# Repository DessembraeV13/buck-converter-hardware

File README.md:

# Przetwornica DC/DC Buck 60V na 5V / 30A z Cyfrowym Sterowaniem
### _High-Power 60V to 5V / 30A Buck Converter with Digital Control Interface_

Projekt i realizacja wysokoprądowej, wysokonapięciowej przetwornicy impulsowej typu Synchronous Buck, zrealizowanej w oprogramowaniu **KiCAD**. Projekt obejmował pełen cykl tworzenia hardware'u: od definicji założeń, przez dobór komponentów, projekt schematu ideowego, aż po projekt wielowarstwowej płytki PCB i uruchomienie fizycznego prototypu.

Celem było stworzenie platformy sprzętowej zdolnej do wydajnej konwersji mocy, przygotowanej do współpracy z mikrokontrolerem w celu cyfrowego sterowania parametrami wyjściowymi.

<div align="center">
  
  <br>
  <em>Rys. 1. Zmontowany i uruchomiony prototyp przetwornicy.</em>
</div>

---

## Główne Założenia i Specyfikacja Techniczna

- **Topologia:** Synchroniczna przetwornica obniżająca napięcie (Synchronous Buck).
- **Napięcie wejściowe (Vin):** do **60V**.
- **Napięcie wyjściowe (Vout):** **5V** (z możliwością regulacji przez mikrokontroler).
- **Maksymalny prąd wyjściowy (Iout_max):** Projektowany do **30A**.
- **Kluczowe komponenty stopnia mocy:**
    - **Sterownik bramek MOSFET:** Texas Instruments LM5106
    - **Tranzystory MOSFET:** Texas Instruments CSD19531KCS (N-Channel NexFET)
- **Sterowanie:** Układ przygotowany do sterowania sygnałem **PWM** z mikrokontrolera (ESP32-S2).
- **Architektura zasilania logiki:** **Dwustopniowa** – pomocnicza przetwornica buck 12V (LM5164) zasila stabilizatory liniowe 5V i 3.3V, zapewniając wysoką sprawność.
- 🔩 **Interfejs komunikacyjny CAN Bus:** Płytka wyposażona w transceiver CAN (TJA1051T), przygotowany do komunikacji w standardach przemysłowych.
- **Płytka PCB:** 4-warstwowa, z dedykowanymi płaszczyznami masy i zasilania w celu optymalizacji termicznej i minimalizacji pętli prądowych.

---

## Architektura Sprzętowa

Projekt hardware'owy został podzielony na trzy oddzielne bloki funkcjonalne.

#### 1. Stopień Wysokiej Mocy
Sekcja odpowiedzialna za główną konwersję energii. Zawiera kluczowe elementy takie jak tranzystory MOSFET, sterownik bramek, cewkę wyjściową oraz kondensatory filtrujące. Projekt ścieżek na PCB w tym obszarze został zoptymalizowany pod kątem przenoszenia dużych prądów (do 30A) i minimalizacji pętli prądowych o wysokiej częstotliwości.

<div align="center">
  
  <br>
  <em>Rys. 2. Schemat ideowy stopnia mocy przetwornicy.</em>
</div>

#### 2. Układ Zasilania
Ten blok odpowiada za dostarczenie stabilnych napięć dla całej logiki cyfrowej. Został zrealizowany w wydajnej, **dwustopniowej architekturze**:
1.  **Pre-regulator:** Główne napięcie wejściowe (do 60V) jest najpierw obniżane do 12V przez dedykowaną przetwornicę buck (LM5164).
2.  **Stabilizatory LDO:** Stabilne, pośrednie napięcie 12V zasila następnie stabilizatory liniowe, które generują czyste linie 5V i 3.3V.

Taka architektura znacząco poprawia sprawność i zarządzanie ciepłem w porównaniu do próby zasilania LDO bezpośrednio z wysokiego napięcia wejściowego.

<div align="center">
  
  <br>
  <em>Rys. 3. Schemat ideowy sekcji zasilania.</em>
</div>

#### 3. Mikrokontroler i Peryferia
Logika urządzenia, oparta o mikrokontroler **ESP32-S2**. Ten blok zawiera również wszystkie interfejsy użytkownika i komunikacyjne, w tym:
- Złącza do programowania i debugowania.
- Diody LED i przyciski do interakcji z użytkownikiem.
- Transceiver magistrali CAN (TJA1051T), implementujący warstwę fizyczną dla niezawodnej komunikacji w standardach przemysłowych.

<div align="center">
  
  <br>
  <em>Rys. 4. Schemat ideowy sekcji sterowania z mikrokontrolerem i peryferiami.</em>
</div>

---

## Projekt Płytki PCB

Projekt 4-warstwowej płytki PCB był kluczowym elementem projektu, mającym na celu zapewnienie stabilności termicznej i elektrycznej przy dużych obciążeniach.

<div align="center">
  
  <br>
  <em>Rys. 5. Render 3D finalnego projektu PCB.</em>
</div>

- **Warstwa 1 (Top):** Główne ścieżki prądowe, komponenty mocy, interfejs użytkownika.
- **Warstwa 2 (GND Plane):** Lita płaszczyzna masy zapewniająca niską impedancję ścieżki powrotnej prądu i doskonałe ekranowanie.
- **Warstwa 3 (GND Plane):** Druga płaszczyzna masy dla dalszej poprawy integralności sygnałowej i odprowadzania ciepła.
- **Warstwa 4 (Bottom):** Mikrokontroler, dodatkowe komponenty, ścieżki sygnałowe.

---

## Uruchomienie i Pomiary

Prototyp został zmontowany i poddany testom w celu weryfikacji poprawności działania. Pomiary oscyloskopowe potwierdziły prawidłowe sterowanie bramek tranzystorów MOSFET. Układ został również pomyślnie przetestowany pod lekkim obciążeniem, stabilnie dostarczając napięcie wyjściowe bliskie 5V przy zasilaniu 60V.

---

## Pliki Projektowe

Pełny projekt hardware'owy (schemat, PCB) jest dostępny w folderze [`project_files/`](project_files/). Można go otworzyć za pomocą darmowego oprogramowania **KiCAD**.

_Uwaga: Oprogramowanie (firmware) dla mikrokontrolera zostało opracowane przez innego członka zespołu i nie jest częścią tego repozytorium. Zaimplementowany hardware magistrali CAN nie był wykorzystywany w finalnej wersji oprogramowania._

---

## Licencja

Ten projekt jest udostępniony na licencji MIT - zobacz plik [LICENSE](LICENSE) po szczegóły.

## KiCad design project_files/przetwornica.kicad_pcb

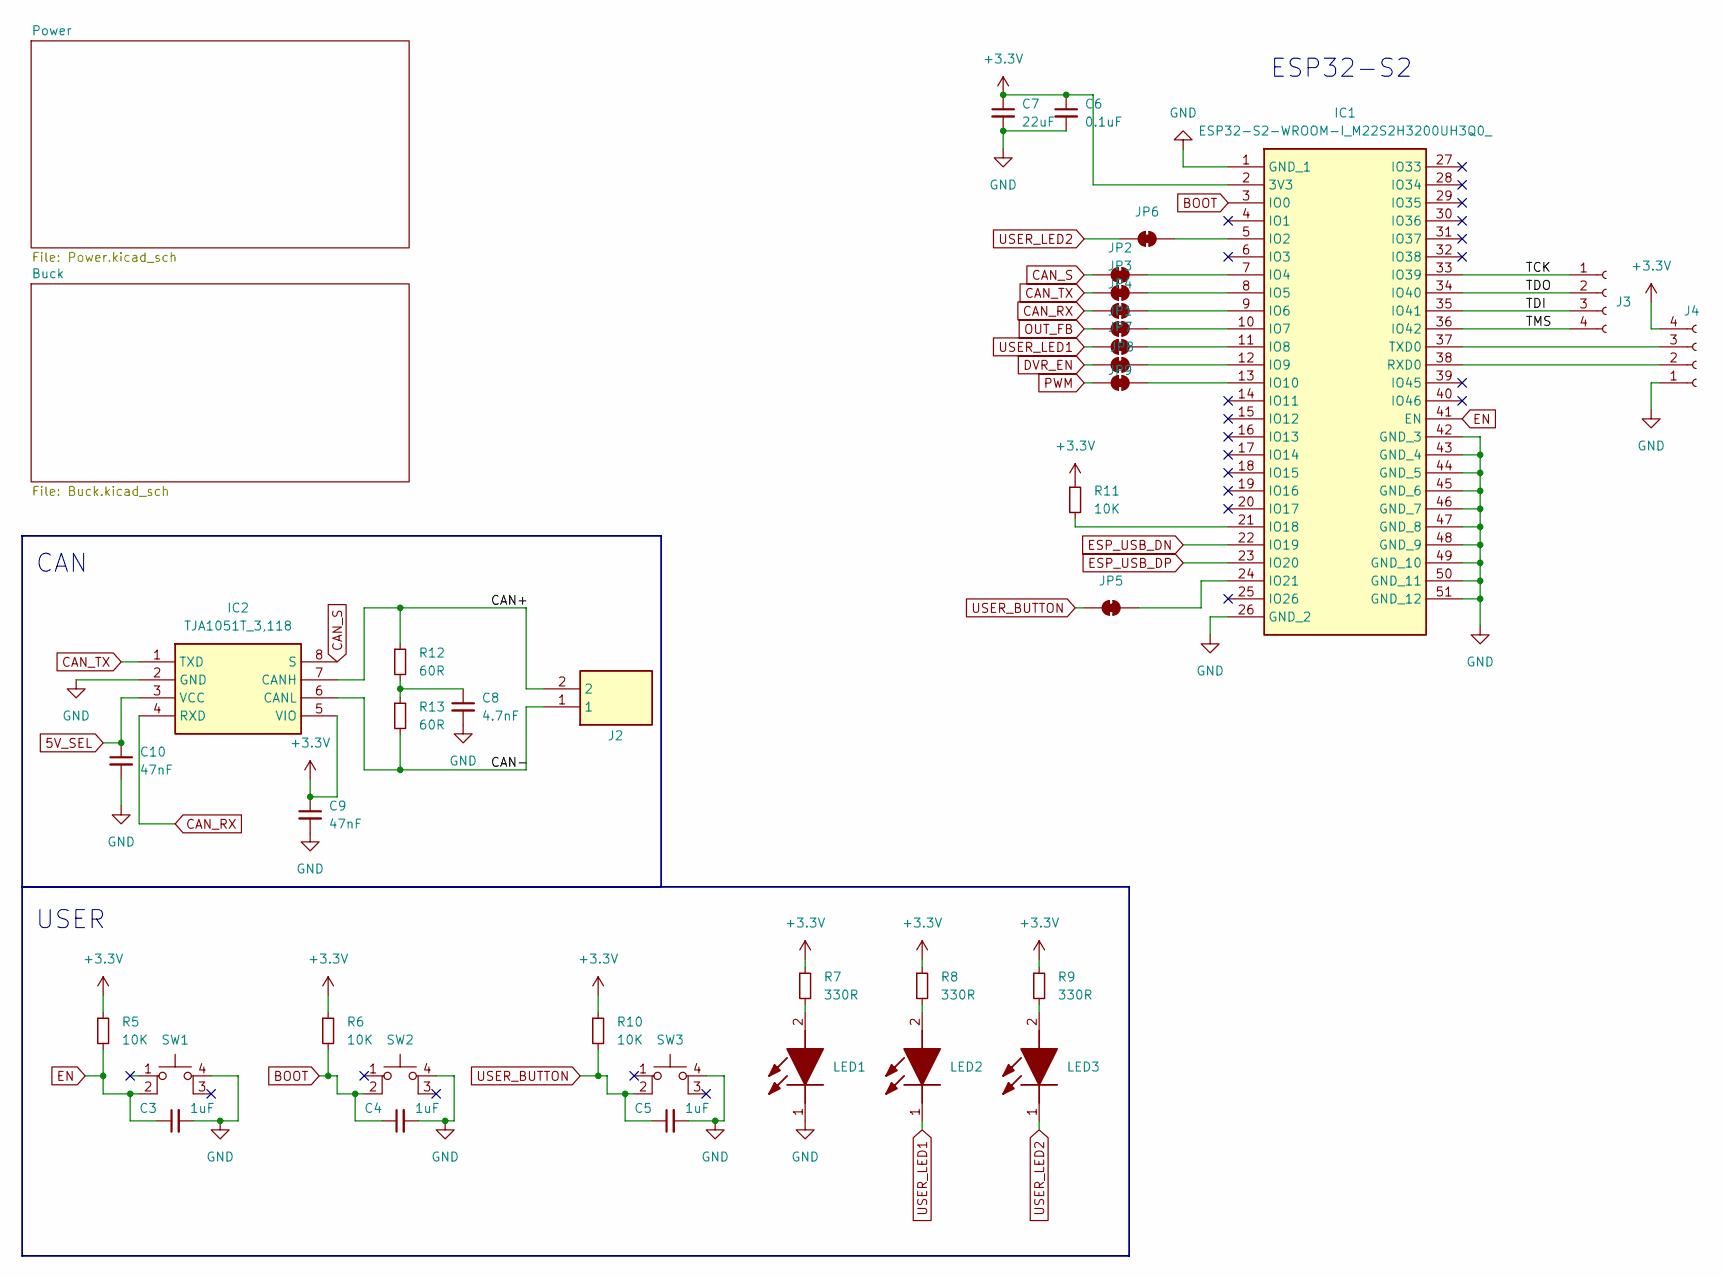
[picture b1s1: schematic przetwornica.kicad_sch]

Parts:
C3, C4, C5: 1uF; C_0805_2012Metric_Pad1.18x1.45mm_HandSolder
C6: 0.1uF; C_0805_2012Metric_Pad1.18x1.45mm_HandSolder
C7: 22uF; C_0805_2012Metric_Pad1.18x1.45mm_HandSolder
C8: 4.7nF; C_0805_2012Metric_Pad1.18x1.45mm_HandSolder
C9, C10: 47nF; C_0805_2012Metric_Pad1.18x1.45mm_HandSolder
IC1: ESP32-S2-WROOM-I_M22S2H3200UH3Q0_; ESP32S2WROOMIM22S2H3200UH3Q0; Manufacturer_Part_Number ESP32-S2-WROOM-I(M22S2H3200UH3Q0)
IC2: TJA1051T_3,118; SOIC127P600X175-8N; Manufacturer_Part_Number TJA1051T/3,118
J2: XY301V-2P__5.00_; XY301V2P500; Manufacturer_Part_Number XY301V-2P (5.00)
J3, J4: Conn_01x04_Socket; PinHeader_1x04_P2.54mm_Vertical
JP1, JP2, JP3, JP4, JP5, JP6, JP7, JP8, JP9: SolderJumper_2_Bridged; SolderJumper-2_P1.3mm_Bridged_RoundedPad1.0x1.5mm
LED1: LTST-C171KRKT; LEDM2012X90N; Manufacturer_Part_Number LTST-C171KRKT
LED2, LED3: LTST-C170KFKT; LEDC2012X120N; Manufacturer_Part_Number LTST-C170KFKT
R5, R6, R10, R11: 10K; R_0805_2012Metric_Pad1.20x1.40mm_HandSolder
R7, R8, R9: 330R; R_0805_2012Metric_Pad1.20x1.40mm_HandSolder
R12, R13: 60R; R_0805_2012Metric_Pad1.20x1.40mm_HandSolder
SW1, SW2, SW3: SW_MEC_5E; 13019319

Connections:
5V_SEL: C10.1, IC2.3 (VCC); also elsewhere on the board
+3.3V: C6.1, C7.1, C9.1, IC1.2 (3V3), IC2.5 (VIO), J4.4, R5.1, R6.1, R7.1, R8.1, R9.1, R10.1, R11.1; also elsewhere on the board
/CAN+: IC2.7 (CANH), J2.2, R12.1
/CAN-: IC2.6 (CANL), J2.1, R13.2
/TCK: IC1.33 (IO39), J3.1
/TDI: IC1.35 (IO41), J3.3
/TDO: IC1.34 (IO40), J3.2
/TMS: IC1.36 (IO42), J3.4
BOOT: C4.1, IC1.3 (IO0), R6.2, SW2.2
CAN_RX: IC2.4 (RXD), JP4.1 (A)
CAN_S: IC2.8 (S), JP2.1 (A)
CAN_TX: IC2.1 (TXD), JP3.1 (A)
DVR_EN: JP8.1 (A); also elsewhere on the board
EN: C3.1, IC1.41 (EN), R5.2, SW1.2
ESP_USB_DN: IC1.22 (IO19); also elsewhere on the board
ESP_USB_DP: IC1.23 (IO20); also elsewhere on the board
GND: C3.2, C4.2, C5.2, C6.2, C7.2, C8.2, C9.2, C10.2, IC1.1 (GND_1), IC1.26 (GND_2), IC1.42 (GND_3), IC1.43 (GND_4), IC1.44 (GND_5), IC1.45 (GND_6), IC1.46 (GND_7), IC1.47 (GND_8), IC1.48 (GND_9), IC1.49 (GND_10), IC1.50 (GND_11), IC1.51 (GND_12), IC2.2 (GND), J4.1, LED1.1 (K), SW1.4 (A), SW2.4 (A), SW3.4 (A); also elsewhere on the board
unnamed: C8.1, R12.2, R13.1
unnamed: IC1.5 (IO2), JP6.2 (B)
unnamed: IC1.7 (IO4), JP2.2 (B)
unnamed: IC1.8 (IO5), JP3.2 (B)
unnamed: IC1.9 (IO6), JP4.2 (B)
unnamed: IC1.10 (IO7), JP1.2 (B)
unnamed: IC1.11 (IO8), JP7.2 (B)
unnamed: IC1.12 (IO9), JP8.2 (B)
unnamed: IC1.13 (IO10), JP9.2 (B)
unnamed: IC1.21 (IO18), R11.2
unnamed: IC1.24 (IO21), JP5.2 (B)
unnamed: IC1.38 (RXD0), J4.2
unnamed: IC1.37 (TXD0), J4.3
unnamed: LED1.2 (A), R7.2
unnamed: LED2.2 (A), R8.2
unnamed: LED3.2 (A), R9.2
OUT_FB: JP1.1 (A); also elsewhere on the board
PWM: JP9.1 (A); also elsewhere on the board
USER_BUTTON: C5.1, JP5.1 (A), R10.2, SW3.2
USER_LED1: JP7.1 (A), LED2.1 (K)
USER_LED2: JP6.1 (A), LED3.1 (K)

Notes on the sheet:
ESP32-S2
CAN
USER

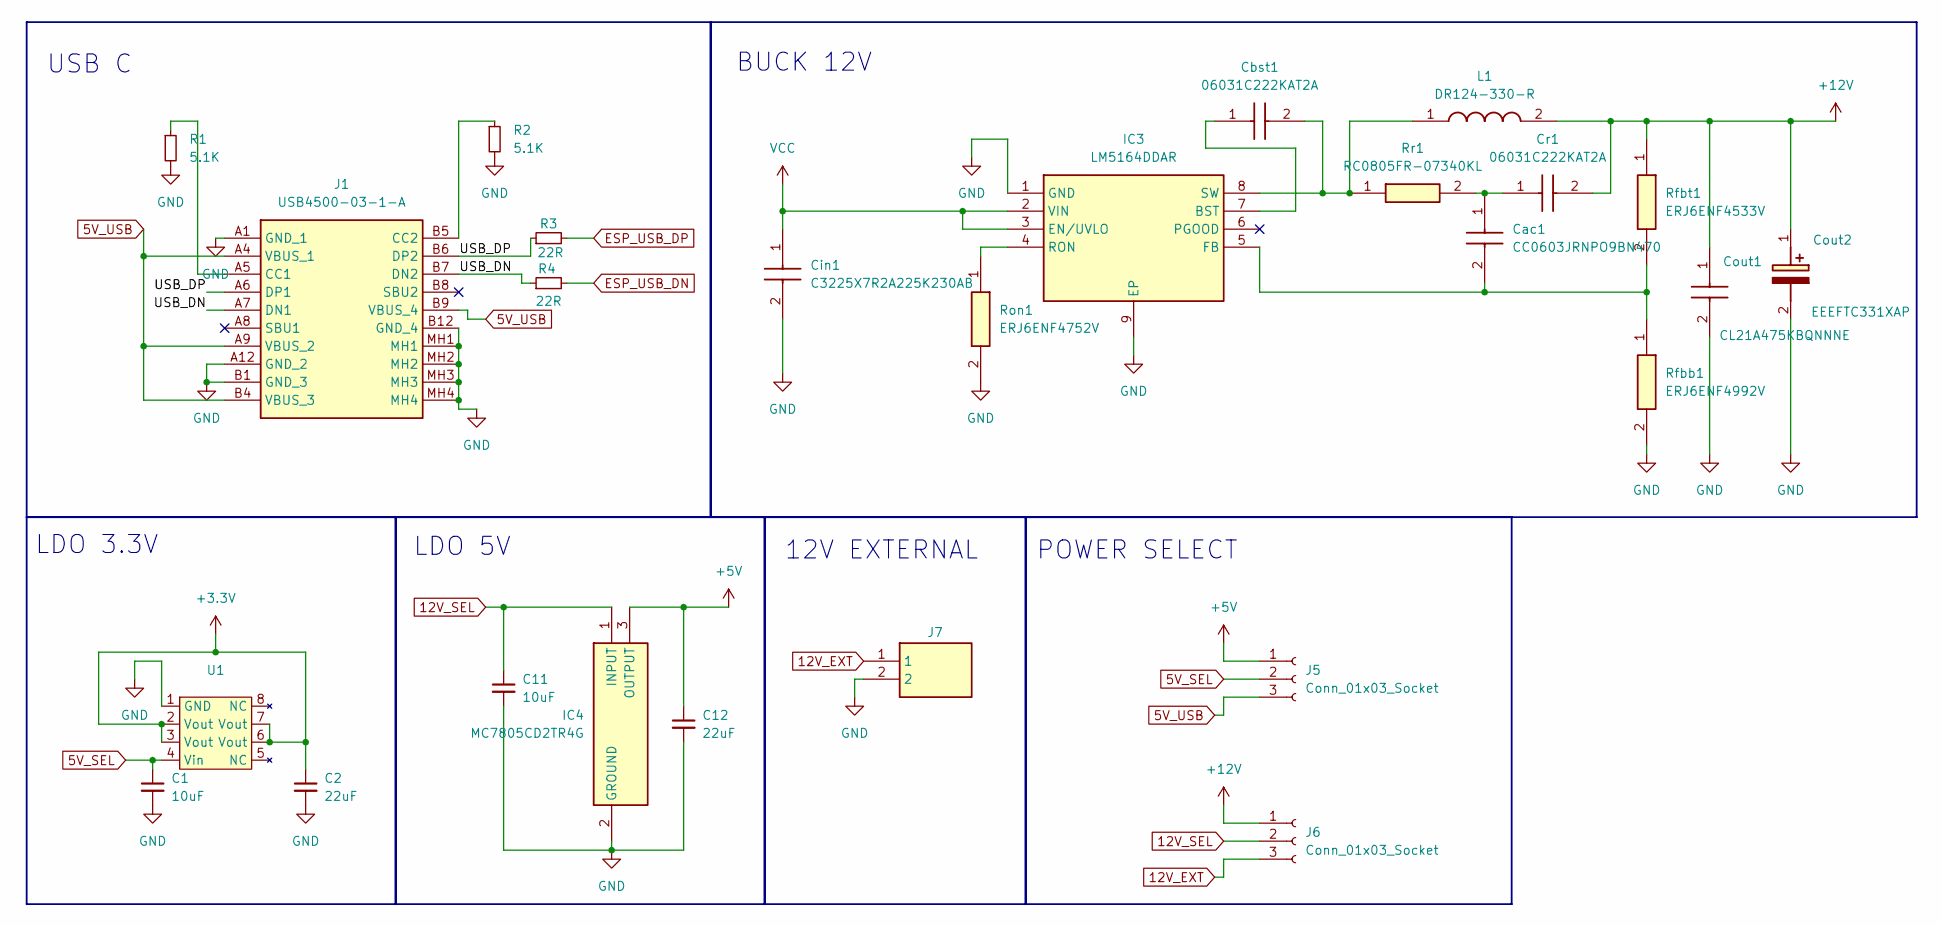
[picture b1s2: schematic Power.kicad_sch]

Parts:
C1, C11: 10uF; C_0805_2012Metric_Pad1.18x1.45mm_HandSolder
C2, C12: 22uF; C_0805_2012Metric_Pad1.18x1.45mm_HandSolder
Cac1: CC0603JRNPO9BN470; CAPC1608X90N; Manufacturer_Part_Number CC0603JRNPO9BN470
Cbst1: 06031C222KAT2A; CAPC1608X90N; Manufacturer_Part_Number 06031C222KAT2A
Cin1: C3225X7R2A225K230AB; CAPC3225X250N; Manufacturer_Part_Number C3225X7R2A225K230AB
Cout1: CL21A475KBQNNNE; CAPC2012X140N; Manufacturer_Part_Number CL21A475KBQNNNE
Cout2: EEEFTC331XAP; EEE0JA331XP; Manufacturer_Part_Number EEEFTC331XAP
Cr1: 06031C222KAT2A; CAPC1608X90N; Manufacturer_Part_Number 06031C222KAT2A
IC3: LM5164DDAR; SOIC127P600X170-9N; Manufacturer_Part_Number LM5164DDAR
IC4: MC7805CD2TR4G; Manufacturer_Part_Number MC7805CD2TR4G
J1: USB4500-03-1-A; USB4500031A; Manufacturer_Part_Number USB4500-03-1-A
J5, J6: Conn_01x03_Socket; PinHeader_1x03_P2.54mm_Vertical
J7: XY301V-2P__5.00_; XY301V2P500; Manufacturer_Part_Number XY301V-2P (5.00)
L1: DR124-330-R; DR124330R; Manufacturer_Part_Number DR124-330-R
R1, R2: 5.1K; R_0805_2012Metric_Pad1.20x1.40mm_HandSolder
R3, R4: 22R; R_0805_2012Metric_Pad1.20x1.40mm_HandSolder
Rfbb1: ERJ6ENF4992V; ERJ6ENF1000V; Manufacturer_Part_Number ERJ6ENF4992V
Rfbt1: ERJ6ENF4533V; ERJ6ENF1000V; Manufacturer_Part_Number ERJ6ENF4533V
Ron1: ERJ6ENF4752V; ERJ6ENF1000V; Manufacturer_Part_Number ERJ6ENF4752V
Rr1: RC0805FR-07340KL; ERJ6ENF1000V; Manufacturer_Part_Number ERJ6ENF4533V
U1: SO-8_3.9x4.9mm_P1.27mm

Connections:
5V_SEL: C1.1, J5.2, U1.4 (Vin); also elsewhere on the board
5V_USB: J1.A4 (VBUS_1), J1.A9 (VBUS_2), J1.B4 (VBUS_3), J1.B9 (VBUS_4), J5.3
12V_EXT: J6.3, J7.1
12V_SEL: C11.1, IC4.1 (INPUT), J6.2; also elsewhere on the board
+3.3V: C2.1, U1.2 (Vout), U1.3 (Vout), U1.6 (Vout), U1.7 (Vout); also elsewhere on the board
+5V: C12.1, IC4.3 (OUTPUT), J5.1
+12V: Cout1.1, Cout2.1 (+), Cr1.2, J6.1, L1.2, Rfbt1.1
/Power/USB_DN: J1.A7 (DN1), J1.B7 (DN2), R4.1
/Power/USB_DP: J1.A6 (DP1), J1.B6 (DP2), R3.1
ESP_USB_DN: R4.2; also elsewhere on the board
ESP_USB_DP: R3.2; also elsewhere on the board
GND: C1.2, C2.2, C11.2, C12.2, Cin1.2, Cout1.2, Cout2.2 (-), IC3.1 (GND), IC3.9 (EP), IC4.2 (GROUND), J1.A1 (GND_1), J1.A12 (GND_2), J1.B1 (GND_3), J1.B12 (GND_4), J1.MH1, J1.MH2, J1.MH3, J1.MH4, J7.2, R1.2, R2.2, Rfbb1.2, Ron1.2, U1.1 (GND); also elsewhere on the board
unnamed: Cac1.1, Cr1.1, Rr1.2
unnamed: Cbst1.1, IC3.7 (BST)
unnamed: Cac1.2, IC3.5 (FB), Rfbb1.1, Rfbt1.2
unnamed: IC3.4 (RON), Ron1.1
unnamed: Cbst1.2, IC3.8 (SW), L1.1, Rr1.1
unnamed: J1.A5 (CC1), R1.1
unnamed: J1.B5 (CC2), R2.1
VCC: Cin1.1, IC3.2 (VIN), IC3.3 (EN/UVLO); also elsewhere on the board

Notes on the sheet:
BUCK 12V
USB C
POWER SELECT
LDO 5V
12V EXTERNAL
LDO 3.3V

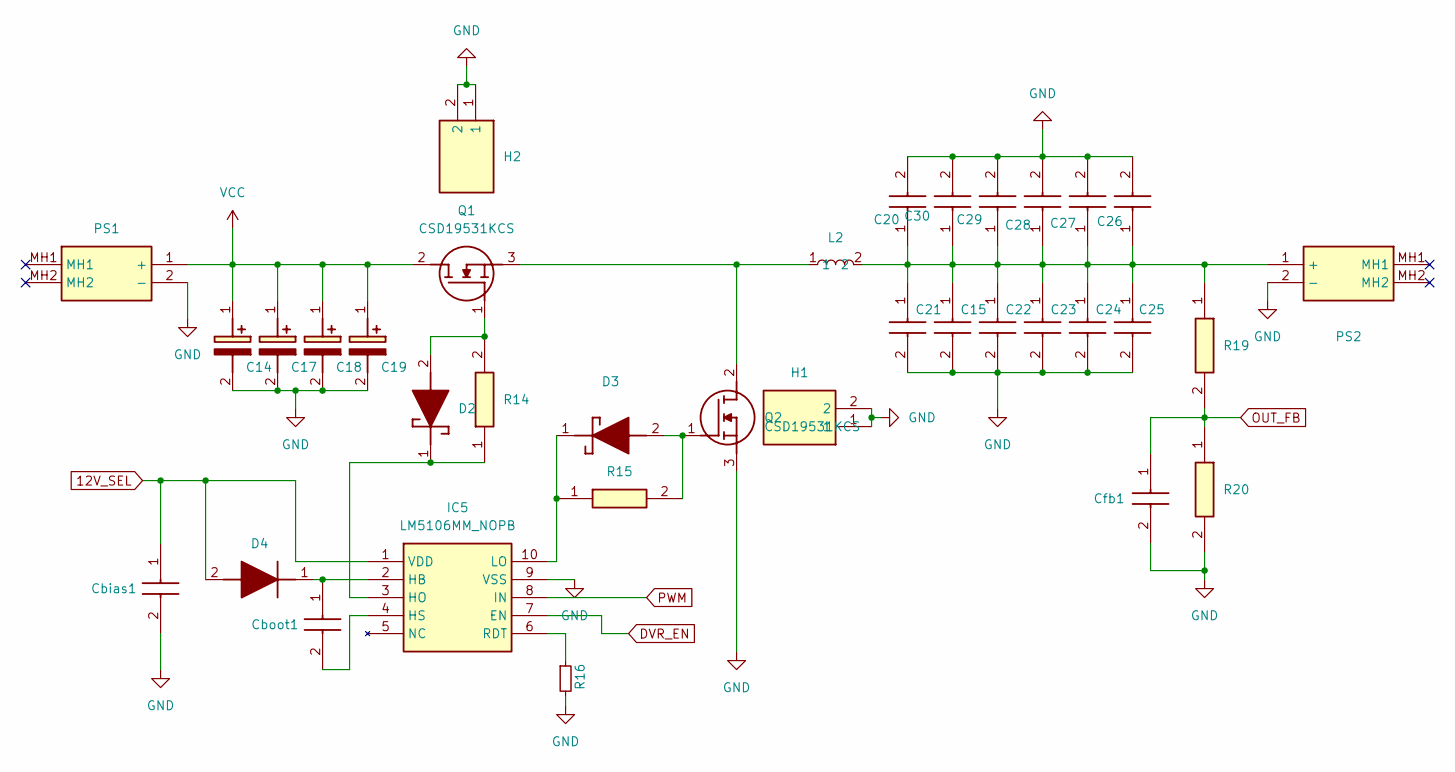
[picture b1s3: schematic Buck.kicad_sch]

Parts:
C14, C17, C18, C19: UCS2C221MHD; CAPPRD750W80D1600H2650; Manufacturer_Part_Number UCS2C221MHD
C15, C22, C23, C24, C25, C26, C27, C28, C29, C30: CL31A106KBHNNNE; CAPC3216X180N; Manufacturer_Part_Number CL31A106KBHNNNE
C20, C21: GYC1V271MCQ1GS; CAPAE1030X1080N; Manufacturer_Part_Number GYC1V271MCQ1GS
Cbias1: CL21A475KBQNNNE; CAPC2012X140N; Manufacturer_Part_Number CL21A475KBQNNNE
Cboot1: CL21A475KBQNNNE; CAPC2012X140N; Manufacturer_Part_Number CL21A475KBQNNNE
Cfb1: CL21A475KBQNNNE; CAPC2012X140N; Manufacturer_Part_Number CL21A475KBQNNNE
D2, D3: SS14_R1_00001; DIOM5027X244N; Manufacturer_Part_Number SS14_R1_00001
D4: BAT46W-7-F; SOD3716X145N; Manufacturer_Part_Number BAT46W-7-F
H1, H2: 657-15ABPE; 65715ABPE; Manufacturer_Part_Number 657-15ABPE
IC5: LM5106MM_NOPB; SOP50P490X110-10N; Manufacturer_Part_Number LM5106MM/NOPB
L2: Cewka
PS1, PS2: XT60PW-M; XT60PWM; Manufacturer_Part_Number XT60PW-M
Q1, Q2: CSD19531KCS; TO254P470X1016X1965-3P; Manufacturer_Part_Number CSD19531KCS
R14, R15: ERJ8BQF6R2V; RESC3116X70N; Manufacturer_Part_Number ERJ8BQF6R2V
R16: 10k; R_0805_2012Metric_Pad1.20x1.40mm_HandSolder
R19, R20: ERJ6ENF4533V; ERJ6ENF1000V; Manufacturer_Part_Number ERJ6ENF4533V

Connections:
12V_SEL: Cbias1.1, D4.2 (A), IC5.1 (VDD); also elsewhere on the board
DVR_EN: IC5.7 (EN); also elsewhere on the board
GND: C14.2 (-), C15.2, C17.2 (-), C18.2 (-), C19.2 (-), C20.2 (-), C21.2 (-), C22.2, C23.2, C24.2, C25.2, C26.2, C27.2, C28.2, C29.2, C30.2, Cbias1.2, Cfb1.2, H1.1, H1.2, H2.1, H2.2, IC5.9 (VSS), PS1.2 (-), PS2.2 (-), Q2.3 (S), R16.2, R20.2; also elsewhere on the board
unnamed: C15.1, C20.1 (+), C21.1 (+), C22.1, C23.1, C24.1, C25.1, C26.1, C27.1, C28.1, C29.1, C30.1, L2.2, PS2.1 (+), R19.1
unnamed: D2.2 (A), Q1.1 (G), R14.2
unnamed: D2.1 (K), IC5.3 (HO), R14.1
unnamed: D3.2 (A), Q2.1 (G), R15.2
unnamed: D3.1 (K), IC5.10 (LO), R15.1
unnamed: Cboot1.1, D4.1 (K), IC5.2 (HB)
unnamed: Cboot1.2, IC5.4 (HS)
unnamed: IC5.6 (RDT), R16.1
unnamed: L2.1, Q1.3 (S), Q2.2 (D)
OUT_FB: Cfb1.1, R19.2, R20.1; also elsewhere on the board
PWM: IC5.8 (IN); also elsewhere on the board
VCC: C14.1 (+), C17.1 (+), C18.1 (+), C19.1 (+), PS1.1 (+), Q1.2 (D); also elsewhere on the board

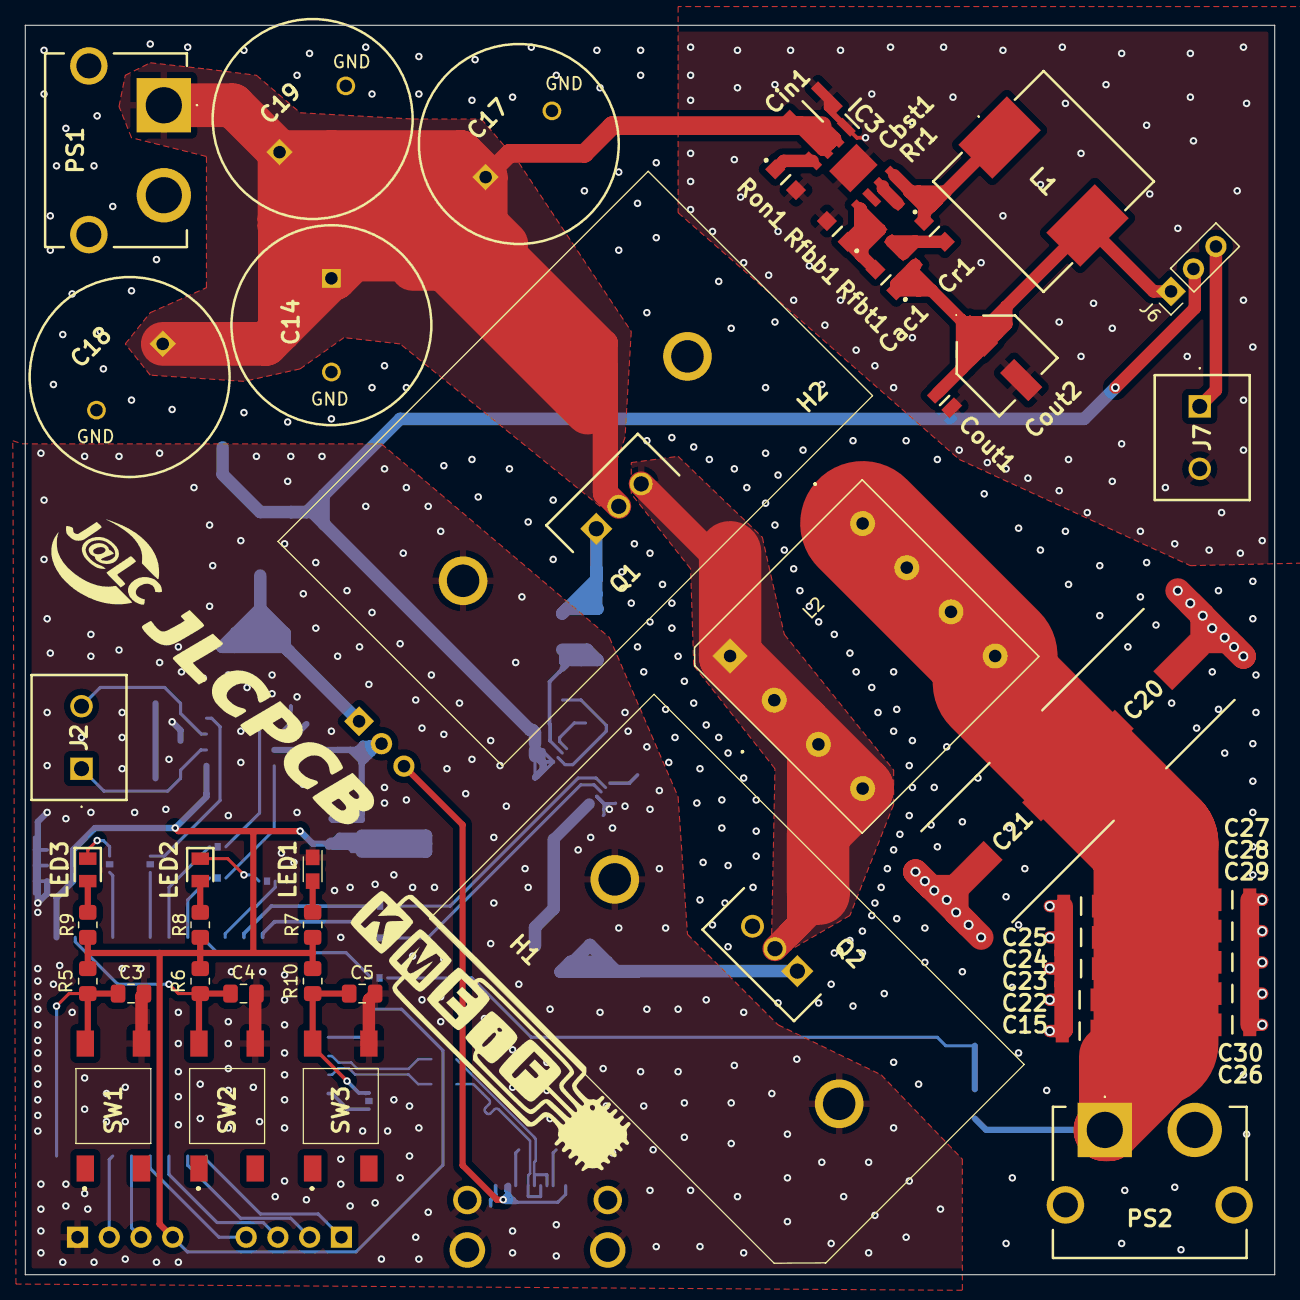
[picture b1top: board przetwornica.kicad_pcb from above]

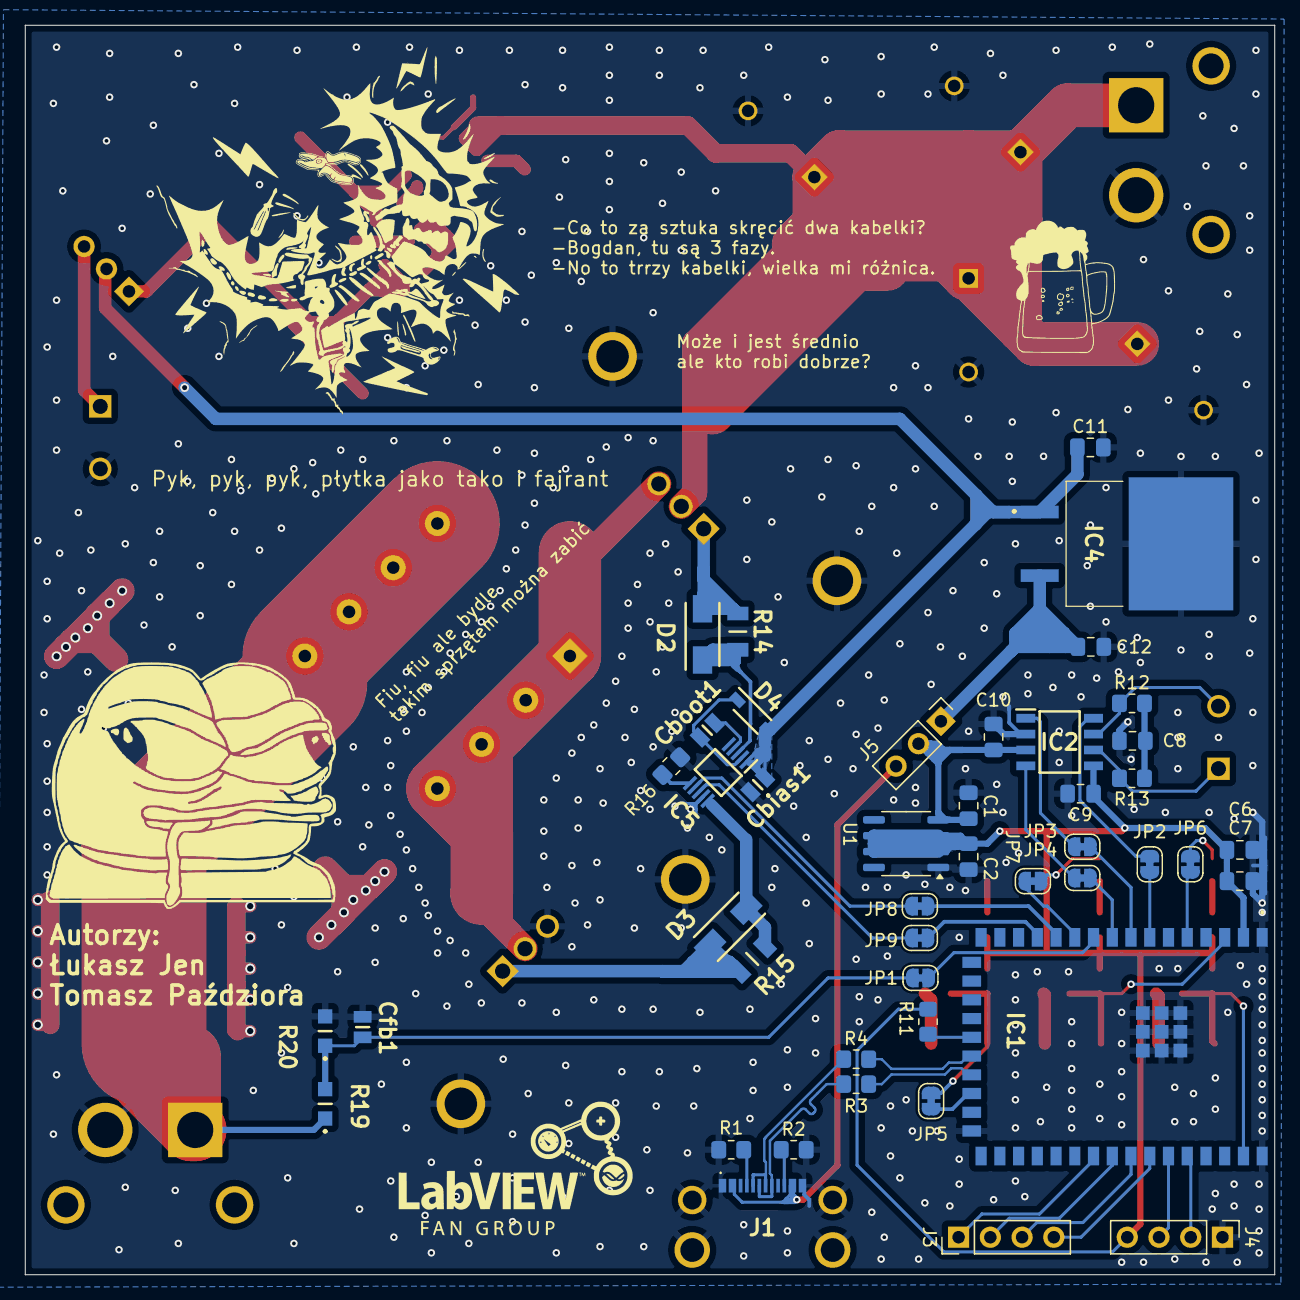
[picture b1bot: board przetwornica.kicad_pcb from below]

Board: 4 copper layers, 100.0 x 100.0 mm, 98 parts (45 on the bottom side), 62 nets.

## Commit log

2025-08-28 Added schematics
